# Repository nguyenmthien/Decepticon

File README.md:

# Decepticon
## an attempt to make an autonomous robot

This repository is currently devided into these sub-folder:
* __ESP32:__ contains main code for ESP32. 
* __Controller:__ contains code and driver for controller for manual robot.
* __AutoClient:__ contains controlling algorithm for autonomous robot.
* __Mechanics:__ contains CAD files of mechanics design and EAGLE files for PCB design.
* __Arduino:__ Archive initial code for Arduino. Everything should work, although require an ESP8266 module to transfer command via Serial. All changes made before 26 March 2019.
* __ESP8266:__ Archive first attemp port to ESP8266 board before the logistics catastrophe. Not sure if everything work. All changes made before 1 April 2019.

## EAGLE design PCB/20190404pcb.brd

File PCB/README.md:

# PCB
Contains EAGLE files for PCB design, best compatible with EAGLE 9.

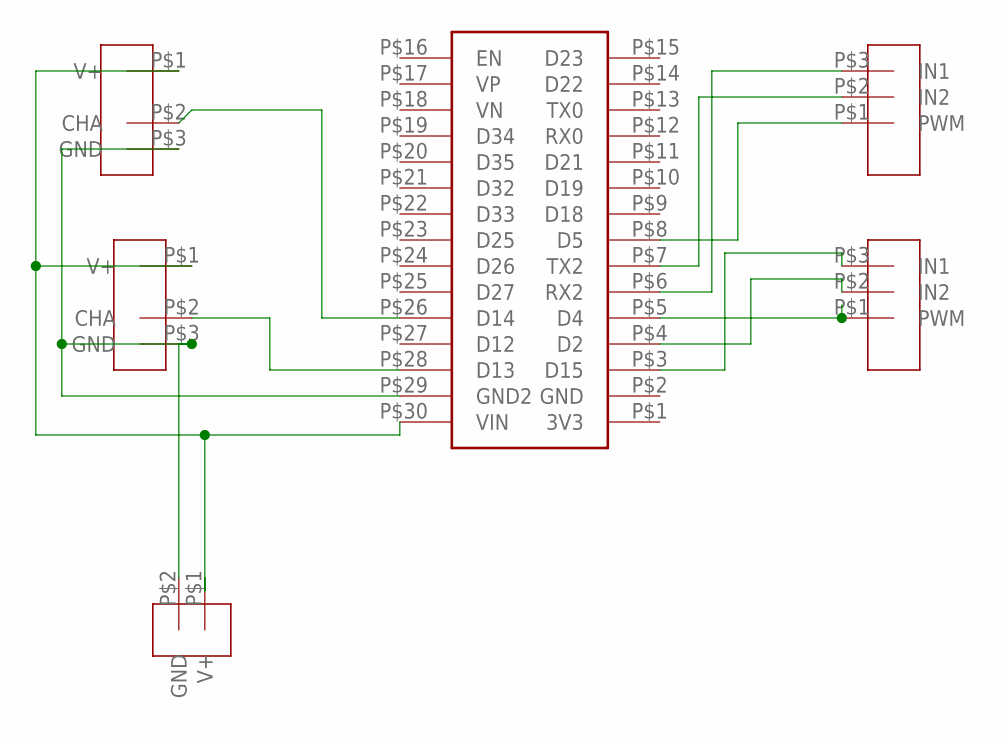
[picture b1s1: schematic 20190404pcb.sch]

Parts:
LE: ENCODER
LM: MOTORDRIVER
RE: ENCODER
RM: MOTORDRIVER
U$1: ESP32
U$9: SOURCE

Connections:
unnamed: RE.P$2 (CHA), U$1.P$26 (D14)
unnamed: LE.P$3 (GND), RE.P$3 (GND), U$1.P$29 (GND2), U$9.P$2 (GND)
unnamed: LE.P$2 (CHA), U$1.P$28 (D13)
unnamed: LE.P$1 (V+), RE.P$1 (V+), U$1.P$30 (VIN), U$9.P$1 (V+)
unnamed: LM.P$3 (IN1), U$1.P$3 (D15)
unnamed: LM.P$2 (IN2), U$1.P$4 (D2)
unnamed: LM.P$1 (PWM), U$1.P$5 (D4)
unnamed: RM.P$3 (IN1), U$1.P$6 (RX2)
unnamed: RM.P$2 (IN2), U$1.P$7 (TX2)
unnamed: RM.P$1 (PWM), U$1.P$8 (D5)

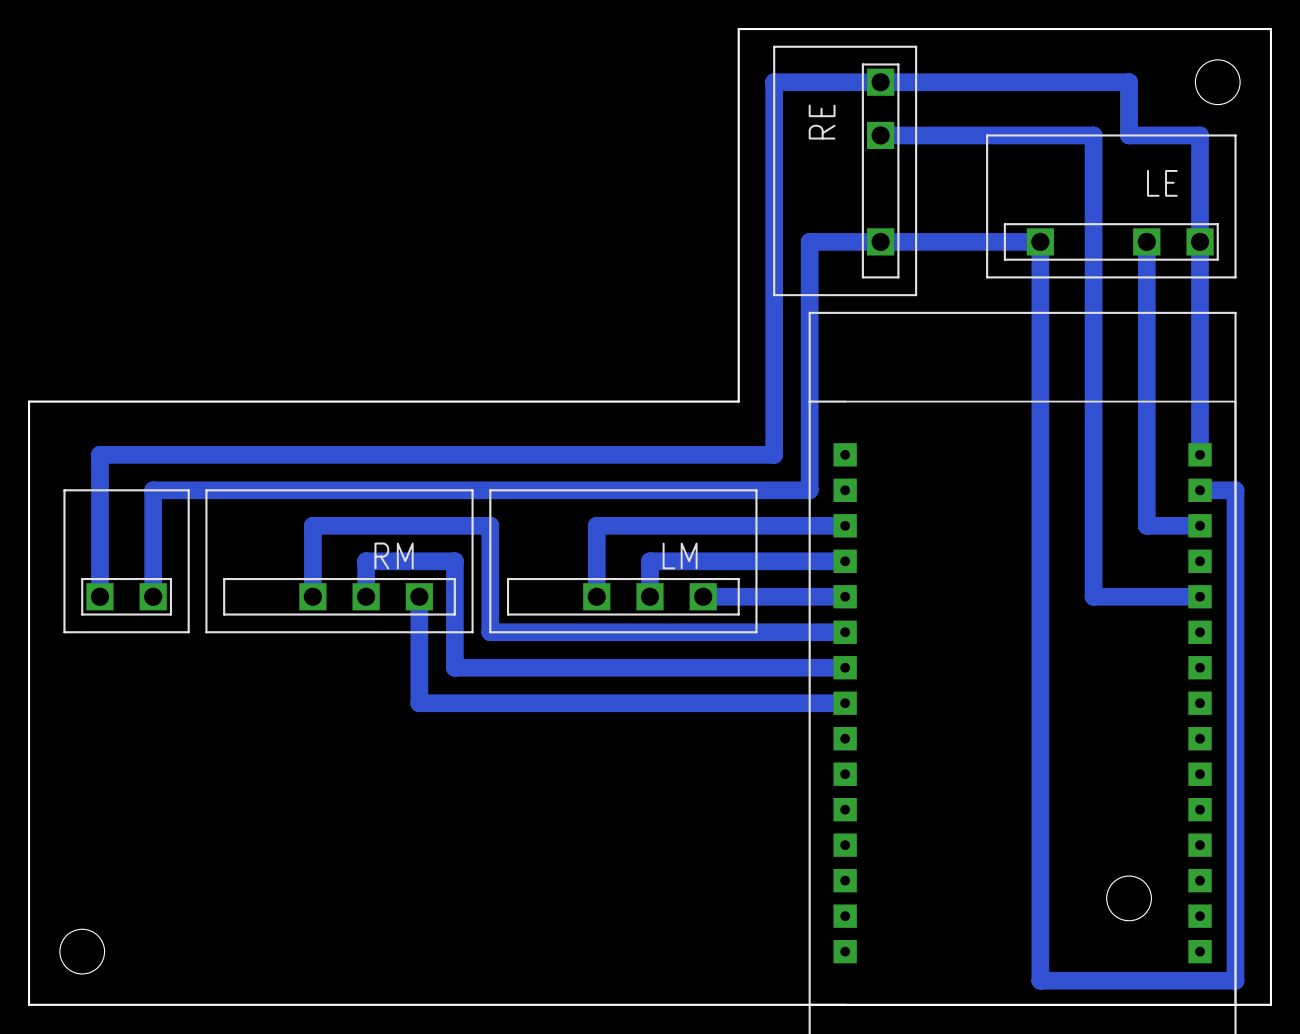
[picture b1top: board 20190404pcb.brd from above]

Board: 2 copper layers, 88.9 x 69.8 mm, 6 parts (0 on the bottom side), 10 nets.

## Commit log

2019-03-31 add README for Arduino
2019-03-31 move code into esp8266 folder
2019-03-31 add README.md to ESP8266
2019-03-31 Revert "Update interpreter.h"
    This reverts commit b8341f56cf7c641ed6ba68a9b610bbcc169fa444.
2019-03-31 Revert "Update interpreter.h"
    This reverts commit 57ce306ab1e16784dd16854e8d1a4927013a368b.
2019-04-01 Change README.md
2019-04-01 add frame for esp32
2019-04-01 remove ESP32/arduino_esp.h
2019-04-02 many change that need undo
2019-04-02 revert /Arduino
2019-04-02 Change in L298N PWM Channel
2019-04-12 new file: .gitignore
2019-04-12 git pull
2019-04-12 change some serial communication to TCP
2019-04-20 change setpoint of pid
2019-04-21 add autoclient folder
2019-04-21 add various file
2019-04-24 Client code from REC, not yet been tested
2019-04-25 add PCB folder
2019-04-25 changed PID variables
2019-05-05 Modify data from server, add point and angle
2019-05-05 new file: AutoClient/visual.py
2019-05-06 Convert origin from top left to mid bot
2019-05-06 Change angle from deg to rad
2019-05-06 comment serial lines
2019-05-07 add speedup and speeddown
2019-05-07 add dictionary
2019-05-07 add server for debugging
2019-05-09 new file: AutoClient/pathfinding.py
2019-05-31 last change
2019-08-17 last commit
